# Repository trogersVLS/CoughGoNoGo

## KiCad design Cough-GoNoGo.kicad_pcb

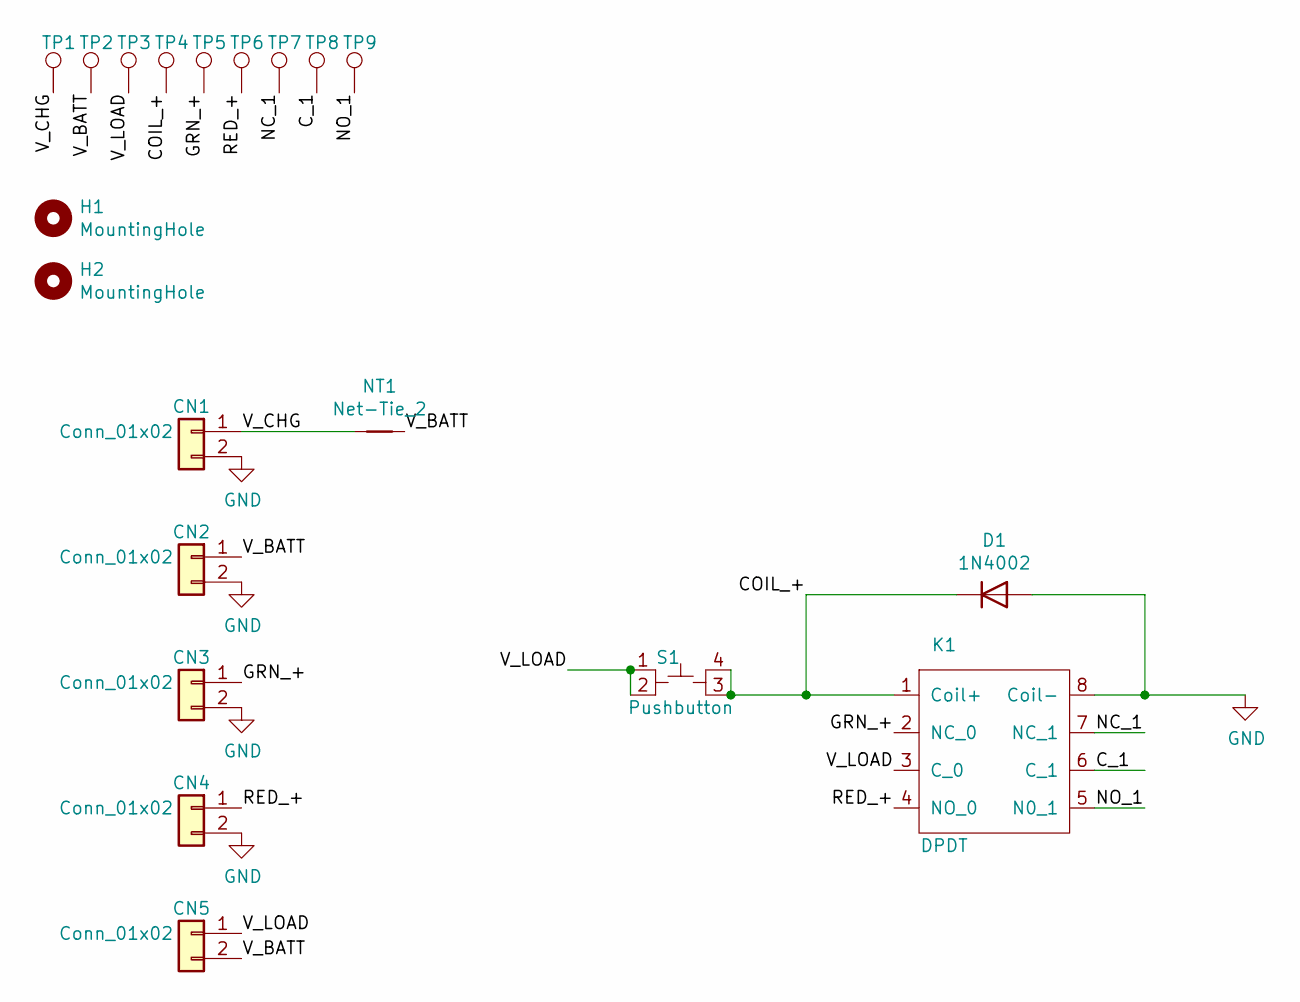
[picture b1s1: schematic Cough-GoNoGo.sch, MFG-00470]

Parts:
CN1, CN2, CN3, CN4, CN5: Conn_01x02; JST_XH_S2B-XH-A_1x02_P2.50mm_Horizontal
D1: 1N4002; D_DO-41_SOD81_P10.16mm_Horizontal
H1, H2: MountingHole; MountingHole_3.2mm_M3_Pad
K1: DPDT; TE_IM04TS
NT1: Net-Tie_2; NetTie-2_SMD_Pad0.5mm
S1: Pushbutton; TactileSwitch
TP1, TP2, TP3, TP4, TP5, TP6, TP7, TP8, TP9: TestPoint; TestPoint_Pad_1.5x1.5mm

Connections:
/COIL_+: D1.1 (K), K1.1 (Coil+), S1.3, S1.4, TP4.1
/C_1: K1.6 (C_1), TP8.1
/GRN_+: CN3.1, K1.2 (NC_0), TP5.1
/NC_1: K1.7 (NC_1), TP7.1
/NO_1: K1.5 (N0_1), TP9.1
/RED_+: CN4.1, K1.4 (NO_0), TP6.1
/V_BATT: CN2.1, CN5.2, NT1.2, TP2.1
/V_CHG: CN1.1, NT1.1, TP1.1
/V_LOAD: CN5.1, K1.3 (C_0), S1.1, S1.2, TP3.1
GND: CN1.2, CN2.2, CN3.2, CN4.2, D1.2 (A), K1.8 (Coil-)

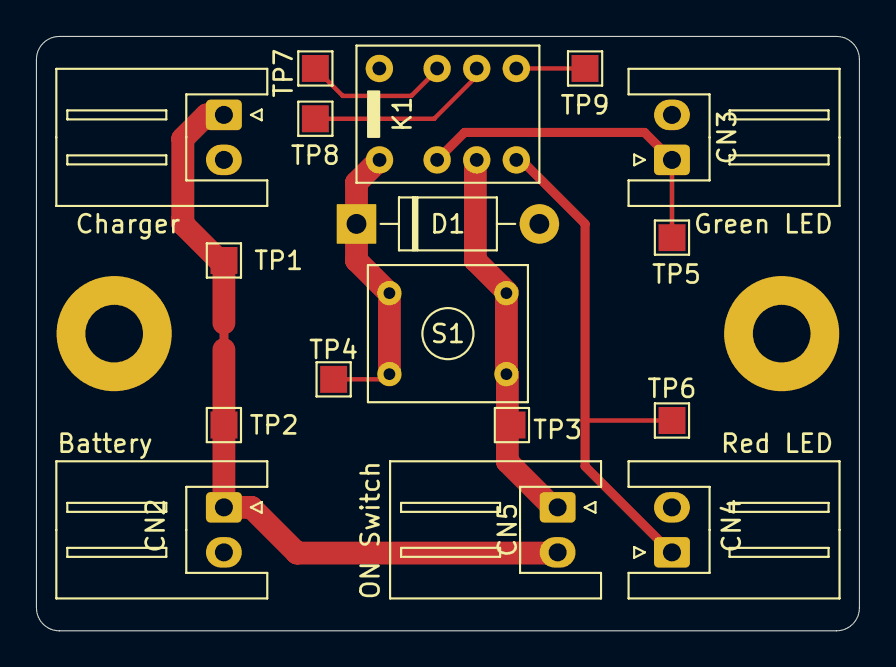
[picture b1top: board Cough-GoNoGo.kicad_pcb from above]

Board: 2 copper layers, 45.7 x 33.0 mm, 20 parts (0 on the bottom side), 10 nets.
